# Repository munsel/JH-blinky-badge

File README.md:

# Jugend Hackt Blink Badge

This is the first verison of a giveaway badge for jugend hackt.
It contains a simple oscillator circuit made up of basic electrical components.

<p align=center>
</img>
</p>

The circuit is called an astable multivibrator and one LED-eye is the inverted output of the other eye.

With two potentiometers and a screwdriver, you can adjust, how long one eye will take till it gets switched off.

## How to assemble
The PCB contains footprints for two kinds of assembly:
1. Through Hole Technology

   Most of the parts can be put through the pcb, wich makes soldering easier.
   Beginners should take this way of assembly.
   
2. Surface Mount Technology

   Parts are layed on the surface of the PCB before soldering.
   Parts are smaller and can slip away while soldering. 
   This is more difficult to solder by hand. Recommended for advanced solderers or if you have an reflow oven.

### THT-version

#### Parts needed

#### Step 0:

#### Step 1:

#### Step 2:

#### Step 3:

#### Step 4:

#### Step 5:

### SMT-version
#### Parts needed

#### Step 0:

#### Step 1:

#### Step 2:

#### Step 3:

#### Step 4:

#### Step 5:

## PCB
The gerber design files are located in the 'production_files'-folder. If you don't want to customize the design, you only need to  send this folder to any manufacturer.

## Parts used
These are the parts used for the THT assembly.

| part | quanitity | vendor |
| ---- | :-------: | -----: |
| battery holder | 1 | [reichelt](https://www.reichelt.de/knopfzellenclip-fuer-20-mm-smd-kzh-20smd-p56574.html?&trstct=pol_3)|
| 47 Ohm resistor | 2 | [reichelt](https://www.reichelt.de/widerstand-kohleschicht-47-ohm-0207-250-mw-5-1-4w-47-p1431.html) |
| 4700 Ohm resistor| 2 | [reichelt](https://www.reichelt.de/widerstand-kohleschicht-4-7-kohm-0207-250-mw-5-1-4w-4-7k-p1425.html) |
| SPST style switch | 1 | [reichelt](https://www.reichelt.de/schiebeschalter-1x-um-stehend-print-rm-2-54-ss-esp101-p112178.html)|
| 500k trim pots | 2 | [reichelt](https://www.reichelt.de/einstellpotentiometer-liegend-500-kohm-9-mm-acp-9-l-500k-p110255.html)|
| 10µF caps | 2 | [reichelt](https://www.reichelt.de/elko-radial-10-uf-50-v-105-c-low-esr-fr-a-10u-50-p200268.html)| 
| LEDs | 2 | [reichelt](https://www.reichelt.de/led-5-mm-bedrahtet-rot-4-5-mcd-60-led-5mm-rt-p10233.html?&trstct=pos_0) |
| NPN Transistor EBC-pinout | 2 | [reichelt](https://www.reichelt.de/bipolartransistor-npn-300v-0-5a-0-625w-to-92-mpsa-42-p13112.html) |

The selected Transistor works, but i am not shure, whether it is the best fit.

For the SMT-version you need different packages:
1. Transistors in SOT-23
2. Resisros in 1206
3. LEDs and Caps in 0805

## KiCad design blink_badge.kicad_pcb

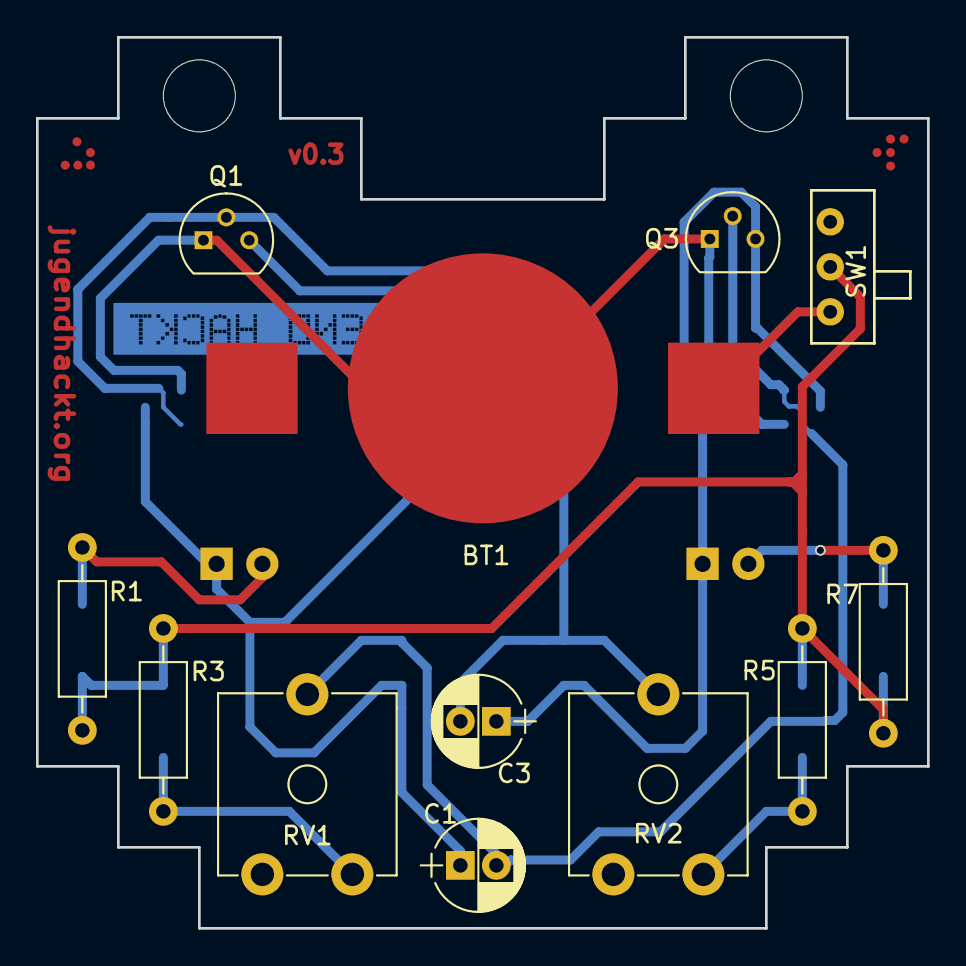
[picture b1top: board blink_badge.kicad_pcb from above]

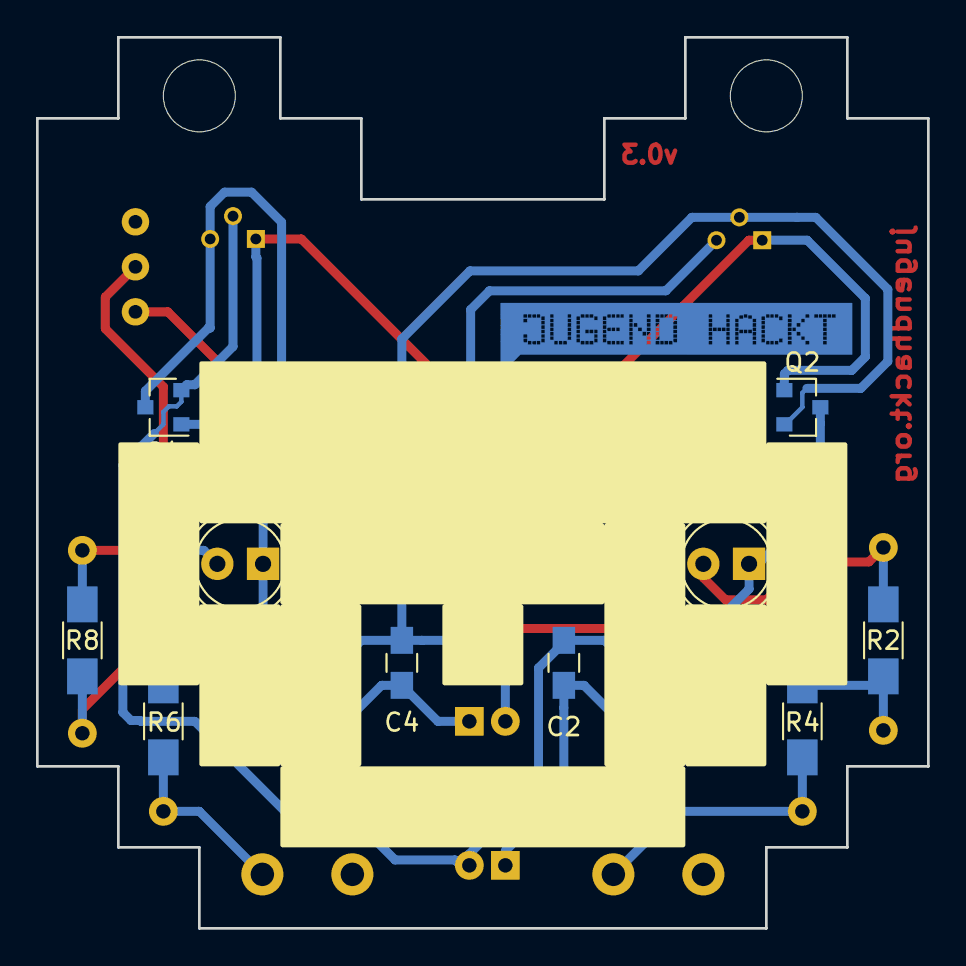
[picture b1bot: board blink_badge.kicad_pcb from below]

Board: 2 copper layers, 49.5 x 49.5 mm, 22 parts (10 on the bottom side), 11 nets.

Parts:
BT1: Battery; coinbattery20mm
C1, C3: CP; CP_Radial_D5.0mm_P2.00mm
C2, C4: C; C_0805_HandSoldering
D1, D2: LED; LED_D5.0mm
Q1, Q3: MPSA42; TO-92_Molded_Narrow
Q2, Q4: MPSA42; SOT-23
R1, R3, R5, R7: R; R_Axial_DIN0207_L6.3mm_D2.5mm_P10.16mm_Horizontal
R2, R4, R6, R8: R; R_1206_HandSoldering
RV1, RV2: POT_TRIM; Potentiometer_Trimmer_ACP_CA9v_Horizontal_Px10.0mm_Py5.0mm
SW1: SPST; switch_mech_alps

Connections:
unnamed: BT1.1, SW1.1
unnamed: BT1.2, Q1.1, Q2.1, Q3.1, Q4.1
unnamed: C1.1, C2.2, D1.1, Q1.3, Q2.3
unnamed: C1.2, C2.1, Q3.2, Q4.2, RV1.2
unnamed: C3.1, C4.1, D2.1, Q3.3, Q4.3
unnamed: C3.2, C4.2, Q1.2, Q2.2, RV2.2
unnamed: D1.2, R1.2, R2.2
unnamed: D2.2, R7.2, R8.2
unnamed: R1.1, R2.1, R3.1, R4.1, R5.1, R6.1, R7.1, R8.1, SW1.2
unnamed: R3.2, R4.2, RV1.1
unnamed: R5.2, R6.2, RV2.1

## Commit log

2018-08-21 initialized
2018-08-21 fixed formatting
2018-08-21 fixed typos in redme
2018-09-05 changed SMT step-order
2018-09-05 added parts to readme
2018-09-05 fixed alignment
2018-09-05 smd directions
2018-09-05 partlist fix
2018-09-05 fixed table rendering
